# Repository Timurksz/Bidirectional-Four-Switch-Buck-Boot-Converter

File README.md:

This repository contains the design files and documentation for a 100W Bidirectional Four Switch Buck-Boost (FSBB) Converter, digitally controlled by the Texas Instruments UCD3138 microprocessor.

Featuring bidirectional energy transfer, this converter is ideal for battery management systems (BMS), automotive applications (48V/12V dual-battery systems), and renewable energy setups.

Project Overview

The topology is based on a non-isolated synchronous four-switch buck-boost converter, capable of operating in two primary modes:
- Buck Mode (48V → 12V): The high-voltage side supplies the low-voltage load.
- Boost Mode (12V → 48V): The low-voltage source transfers energy back to the 48V bus.

The system is digitally controlled using the UCD3138 microprocessor, enabling:
- Closed-loop voltage regulation
- PWM generation
- Bidirectional mode management
- Protection algorithms
- Real-time monitoring

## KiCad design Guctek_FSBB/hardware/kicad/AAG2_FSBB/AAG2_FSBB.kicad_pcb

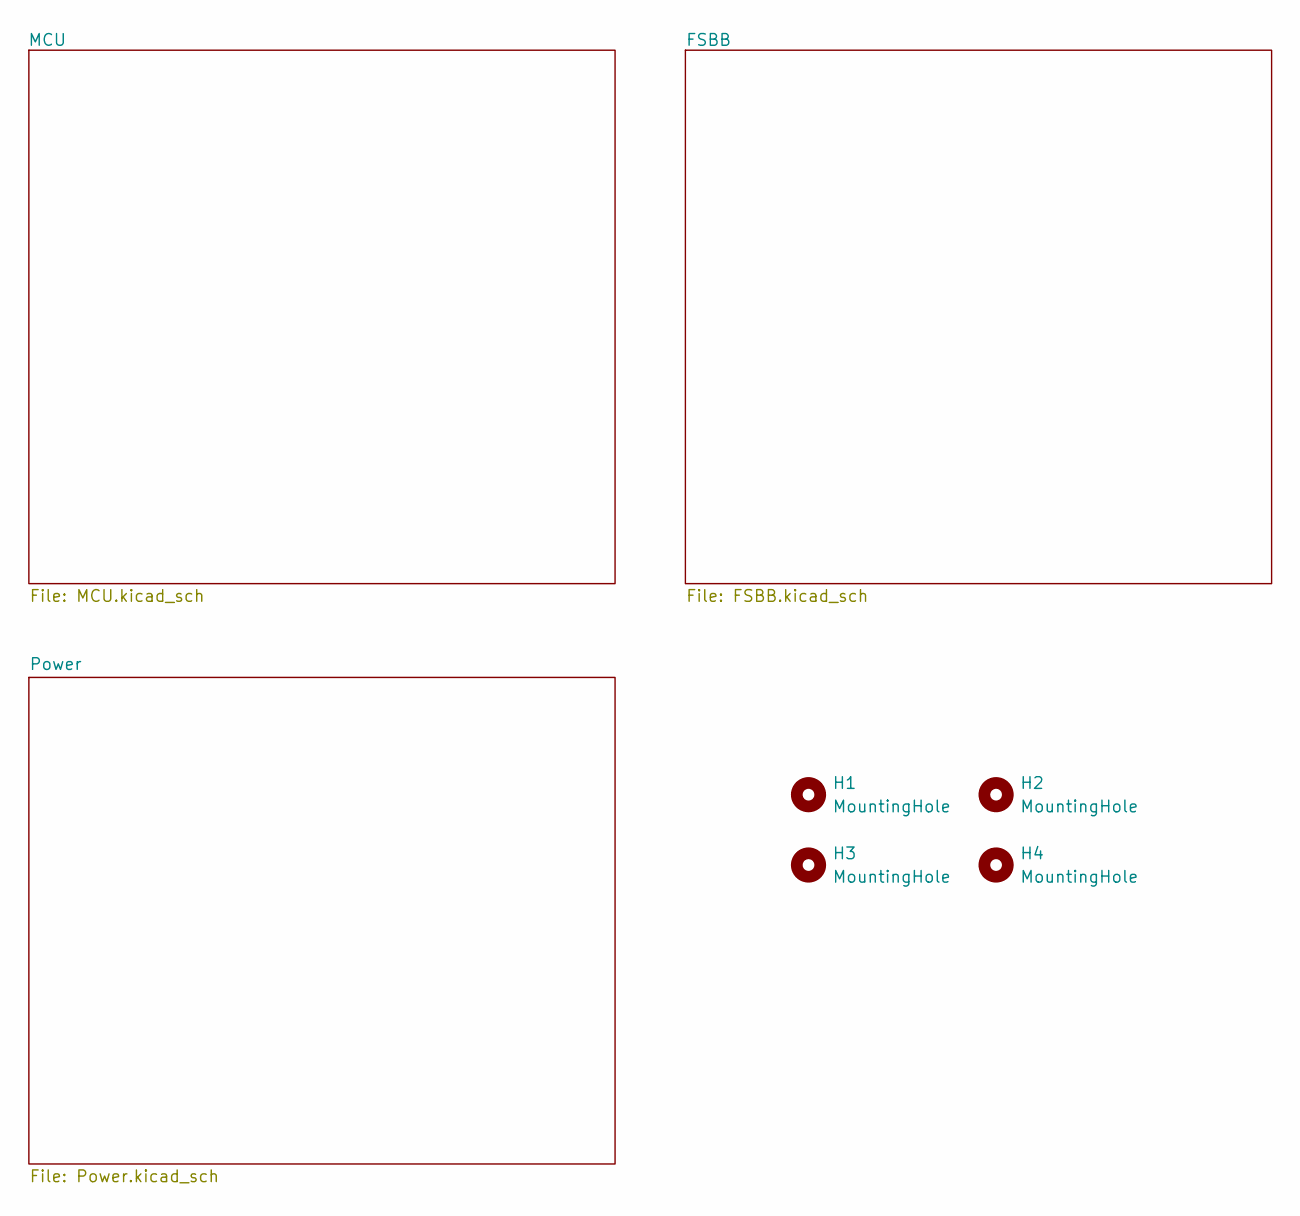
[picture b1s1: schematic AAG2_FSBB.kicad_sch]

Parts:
H1, H2, H3, H4: MountingHole; MountingHole_2.5mm_Pad

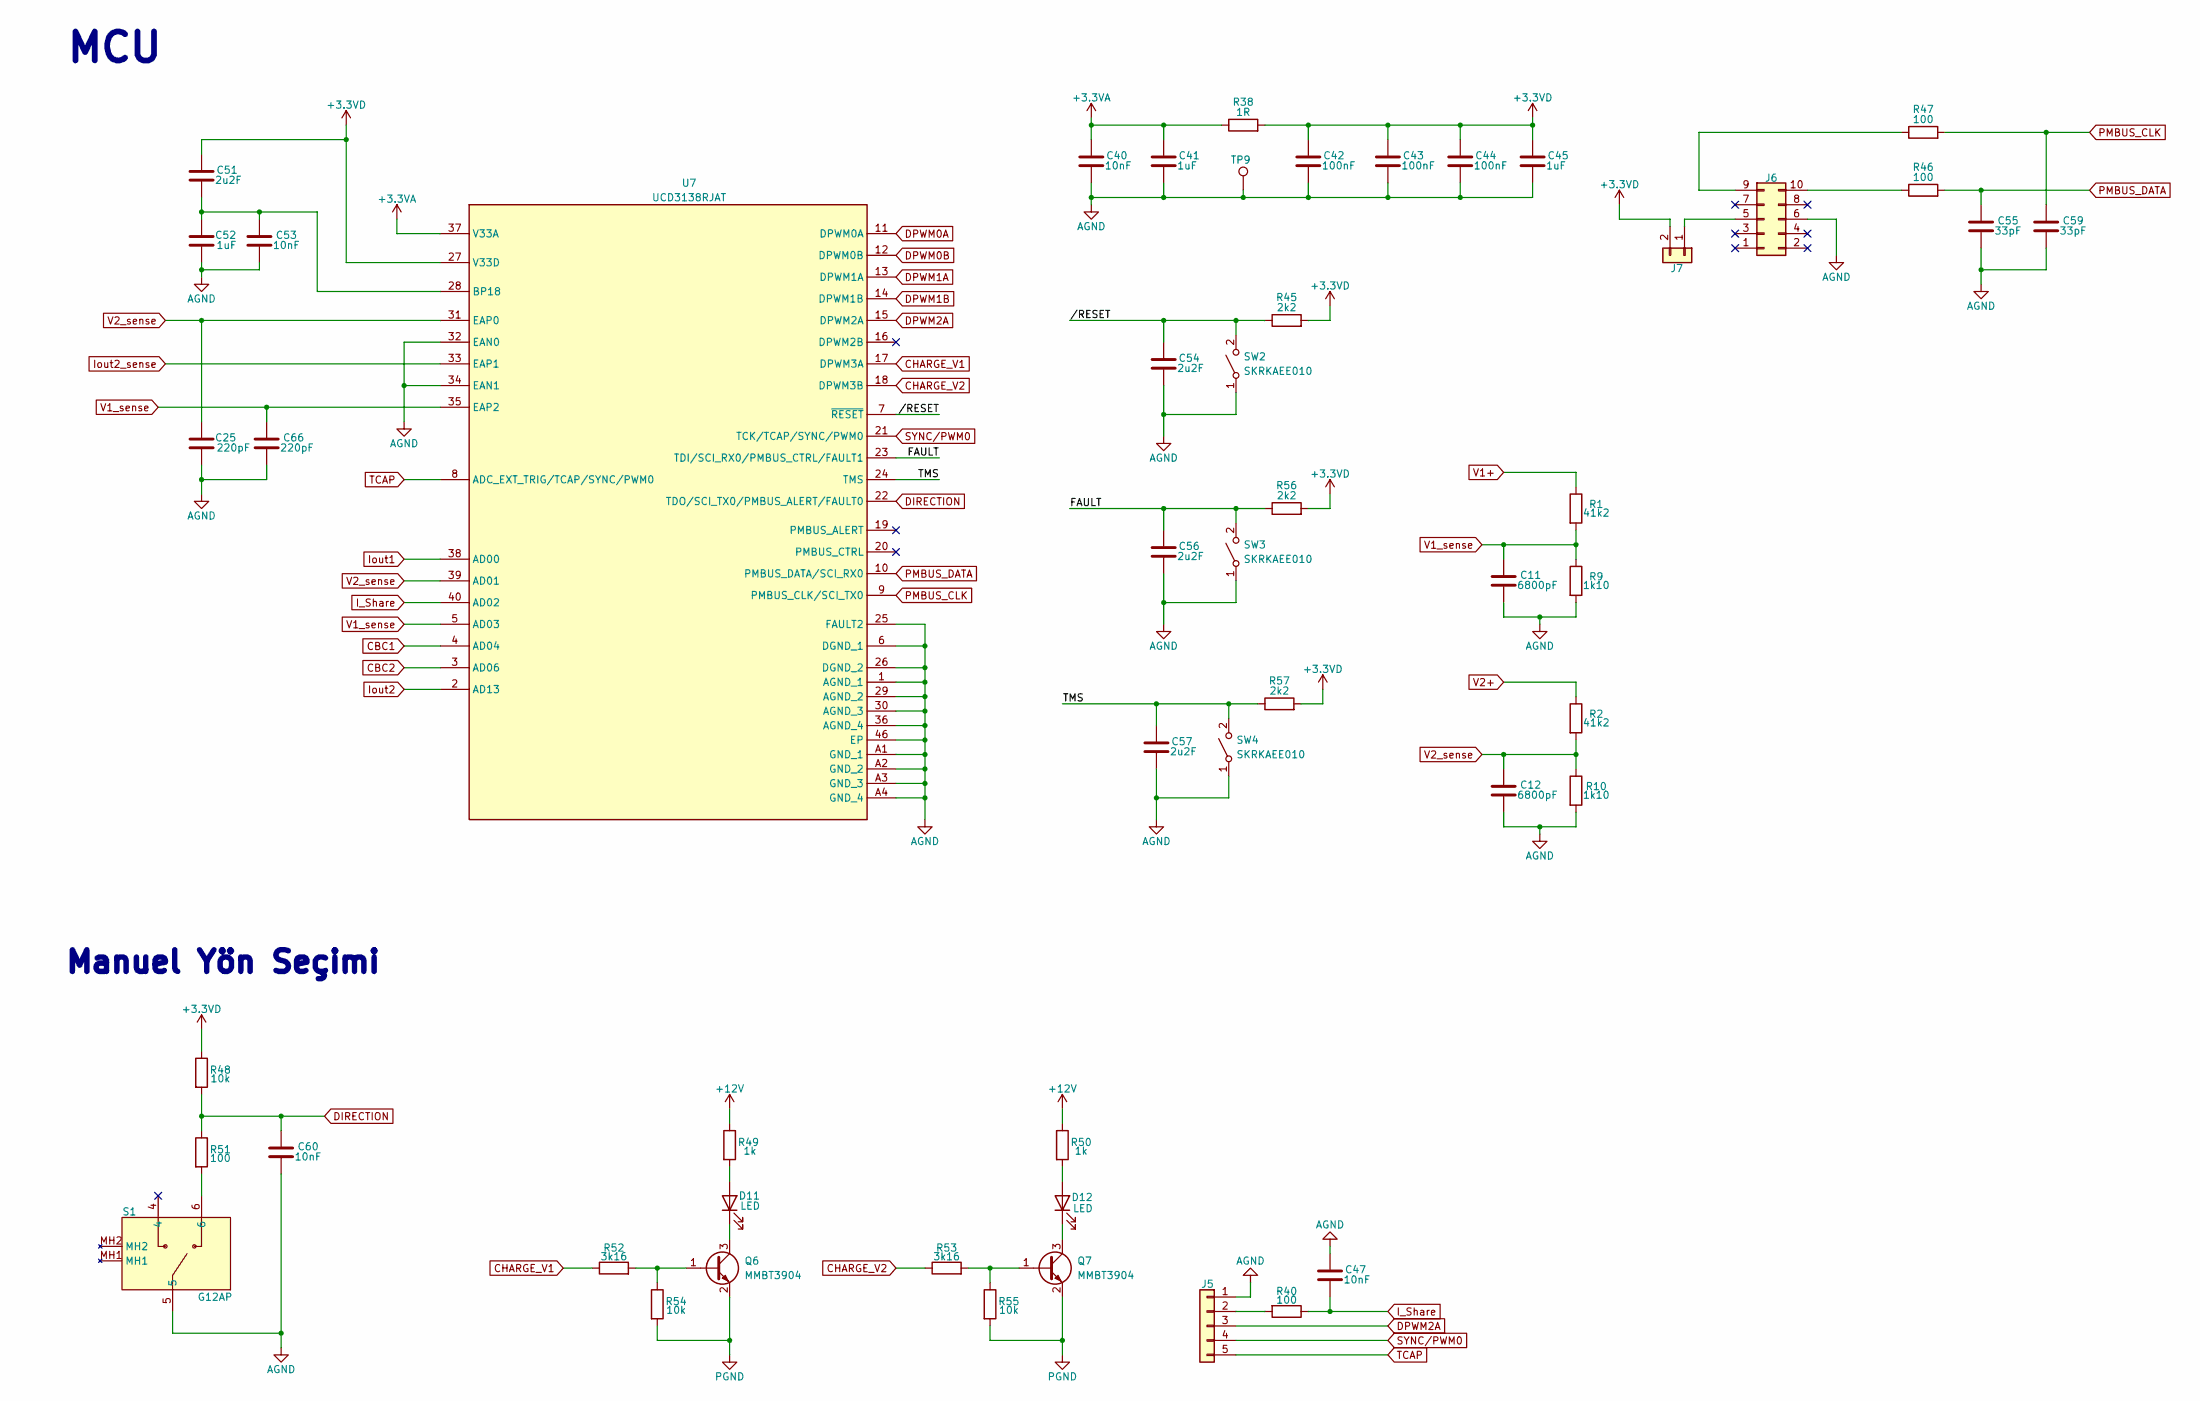
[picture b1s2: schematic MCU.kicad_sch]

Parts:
C11, C12: 6800pF; C_0603_1608Metric
C25, C66: 220pF; C_0603_1608Metric
C40, C47, C53, C60: 10nF; C_0603_1608Metric
C41, C45, C52: 1uF; C_0603_1608Metric
C42, C43, C44: 100nF; C_0603_1608Metric
C51, C54, C56, C57: 2u2F; C_0603_1608Metric
C55, C59: 33pF; C_0603_1608Metric
D11, D12: LED; LED_0805_2012Metric
J5: Conn_01x05; PinHeader_1x05_P1.00mm_Vertical
J6: 5103308-1
J7: Conn_01x02; PinHeader_01x02_P2.54mm_Vertical_THT_D1mm
Q6, Q7: MMBT3904; SOT-23
R1, R2: 41k2; R_0603_1608Metric
R9, R10: 1k10; R_0603_1608Metric
R38: 1R; R_0603_1608Metric
R40, R46, R47, R51: 100; R_0603_1608Metric
R45, R56, R57: 2k2; R_0603_1608Metric
R48, R54, R55: 10k; R_0603_1608Metric
R49, R50: 1k; R_0603_1608Metric
R52, R53: 3k16; R_0603_1608Metric
S1: G12AP; Manufacturer_Part_Number G12AP; Mouser Part Number 633-G12AP
SW2, SW3, SW4: SKRKAEE010
TP9: TestPoint; TestPoint_Pad_1.0x1.0mm
U7: UCD3138RJAT; Manufacturer_Part_Number UCD3138RJAT; Mouser Part Number 595-UCD3138RJAT

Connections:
+3.3VA: C40.1, C41.1, R38.1, U7.37 (V33A)
+3.3VD: C42.1, C43.1, C44.1, C45.1, C51.1, J7.2, R38.2, R45.2, R48.1, R56.2, R57.2, U7.27 (V33D); also elsewhere on the board
+12V: R49.1, R50.1; also elsewhere on the board
/MCU/FAULT: C56.1, R56.1, SW3.2 (B), U7.23 (TDI/SCI_RX0/PMBUS_CTRL/FAULT1)
/MCU/TMS: C57.1, R57.1, SW4.2 (B), U7.24 (TMS)
/MCU//RESET: C54.1, R45.1, SW2.2 (B), U7.7 (~RESET)
AGND: C11.2, C12.2, C25.2, C40.2, C41.2, C42.2, C43.2, C44.2, C45.2, C47.1, C52.2, C53.2, C54.2, C55.2, C56.2, C57.2, C59.2, C60.2, C66.2, J5.1, J6.6, R9.2, R10.2, S1.5, SW2.1 (A), SW3.1 (A), SW4.1 (A), TP9.1, U7.1 (AGND_1), U7.6 (DGND_1), U7.25 (FAULT2), U7.26 (DGND_2), U7.29 (AGND_2), U7.30 (AGND_3), U7.32 (EAN0), U7.34 (EAN1), U7.36 (AGND_4), U7.46 (EP), U7.A1 (GND_1), U7.A2 (GND_2), U7.A3 (GND_3), U7.A4 (GND_4); also elsewhere on the board
CBC1: U7.4 (AD04); also elsewhere on the board
CBC2: U7.3 (AD06); also elsewhere on the board
CHARGE_V1: R52.1, U7.17 (DPWM3A)
CHARGE_V2: R53.1, U7.18 (DPWM3B)
DIRECTION: C60.1, R48.2, R51.1, U7.22 (TDO/SCI_TX0/PMBUS_ALERT/FAULT0)
DPWM0A: U7.11 (DPWM0A); also elsewhere on the board
DPWM0B: U7.12 (DPWM0B); also elsewhere on the board
DPWM1A: U7.13 (DPWM1A); also elsewhere on the board
DPWM1B: U7.14 (DPWM1B); also elsewhere on the board
DPWM2A: J5.3, U7.15 (DPWM2A)
I_Share: C47.2, R40.1, U7.40 (AD02)
Iout1: U7.38 (AD00); also elsewhere on the board
Iout2: U7.2 (AD13); also elsewhere on the board
Iout2_sense: U7.33 (EAP1); also elsewhere on the board
unnamed: D11.2 (A), R49.2
unnamed: D11.1 (K), Q6.3 (C)
unnamed: D12.2 (A), R50.2
unnamed: D12.1 (K), Q7.3 (C)
unnamed: J5.2, R40.2
unnamed: J6.5, J7.1
unnamed: J6.9, R47.1
unnamed: J6.10, R46.1
unnamed: Q6.1 (B), R52.2, R54.1
unnamed: Q7.1 (B), R53.2, R55.1
unnamed: R51.2, S1.6
unnamed: C51.2, C52.1, C53.1, U7.28 (BP18)
PGND: Q6.2 (E), Q7.2 (E), R54.2, R55.2; also elsewhere on the board
PMBUS_CLK: C59.1, R47.2, U7.9 (PMBUS_CLK/SCI_TX0)
PMBUS_DATA: C55.1, R46.2, U7.10 (PMBUS_DATA/SCI_RX0)
SYNC/PWM0: J5.4, U7.21 (TCK/TCAP/SYNC/PWM0)
TCAP: J5.5, U7.8 (ADC_EXT_TRIG/TCAP/SYNC/PWM0)
V1+: R1.1; also elsewhere on the board
V1_sense: C11.1, C66.1, R1.2, R9.1, U7.5 (AD03), U7.35 (EAP2)
V2+: R2.1; also elsewhere on the board
V2_sense: C12.1, C25.1, R2.2, R10.1, U7.31 (EAP0), U7.39 (AD01)

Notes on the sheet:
MCU
Manuel Yön Seçimi

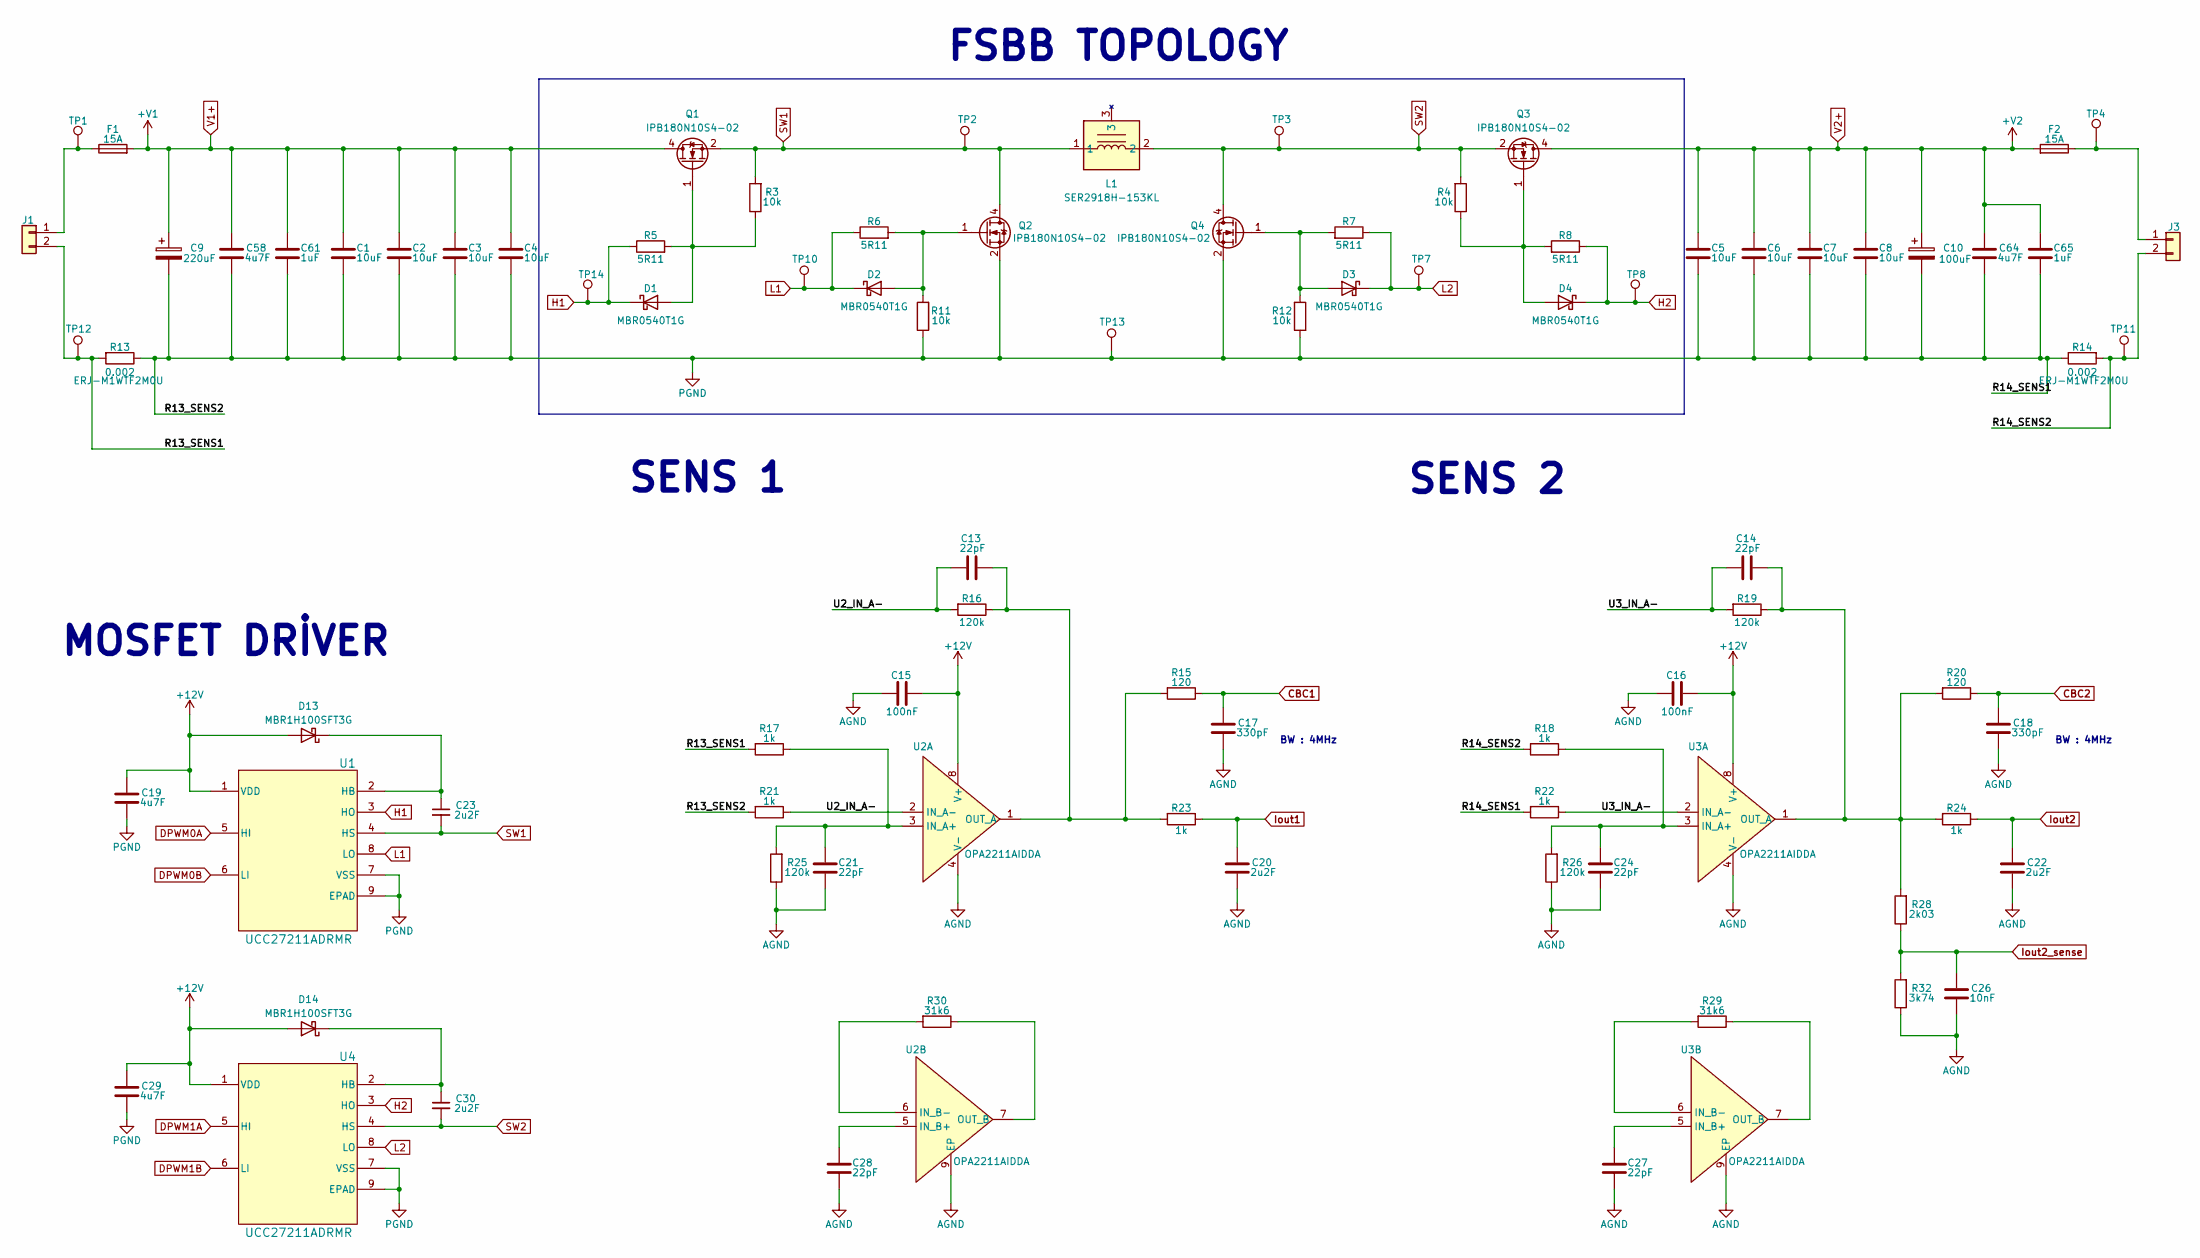
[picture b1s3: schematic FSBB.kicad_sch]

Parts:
C1, C2, C3, C4, C5, C6, C7, C8: 10uF; C_2220_5750Metric
C9: 220uF; EEEFK0J332AQ
C10: 100uF; CAPAE1300X1380N
C13, C14, C21, C24, C27, C28: 22pF; C_0603_1608Metric
C15, C16: 100nF; C_0603_1608Metric
C17, C18: 330pF; C_0603_1608Metric
C19, C29: 4u7F; C_0805_2012Metric
C20, C22: 2u2F; C_0603_1608Metric
C23, C30: 2u2F; C_1206_3216Metric
C26: 10nF; C_0603_1608Metric
C58, C64: 4u7F; C_1210_3225Metric
C61, C65: 1uF; C_1206_3216Metric
D1, D2, D3, D4: MBR0540T1G; D_SOD-123
D13, D14: MBR1H100SFT3G; SODFL3616X98N
F1, F2: 15A; SS_BEL
J1, J3: Conn_01x02; ED1202DS
L1: SER2918H-153KL; SER2918H333KL; Manufacturer_Part_Number SER2918H-153KL; Mouser Part Number 994-SER2918H-153KL
Q1, Q2, Q3, Q4: IPB180N10S4-02; TO-263-6
R3, R4, R11, R12: 10k; R_0603_1608Metric
R5, R6, R7, R8: 5R11; R_0805_2012Metric
R13, R14: 0.002; R_2512_6332Metric
R15, R20: 120; R_0603_1608Metric
R16, R19, R25, R26: 120k; R_0603_1608Metric
R17, R18, R21, R22, R23, R24: 1k; R_0603_1608Metric
R28: 2k03; R_0603_1608Metric
R29, R30: 31k6; R_0603_1608Metric
R32: 3k74; R_0603_1608Metric
TP1, TP2, TP3, TP4, TP7, TP8, TP10, TP11, TP12, TP13, TP14: TestPoint; TestPoint_Pad_1.0x1.0mm
U1, U4: UCC27211ADRMR; DRM8_3P38X2P45_TEX
U2, U3: OPA2211AIDDA; SOIC127P600X170-9N

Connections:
+12V: C15.2, C16.2, C19.1, C29.1, D13.2 (A), D14.2 (A), U1.1 (VDD), U2.8 (V+), U3.8 (V+), U4.1 (VDD); also elsewhere on the board
/FSBB/R13_SENS1: J1.2, R13.2, R17.2, TP12.1; also elsewhere on the board
/FSBB/R14_SENS2: J3.2, R14.2, R18.2, TP11.1; also elsewhere on the board
/FSBB/U2_IN_A-: C13.1, R16.2, R21.1, U2.2 (IN_A-)
/FSBB/U3_IN_A-: C14.1, R19.2, R22.1, U3.2 (IN_A-)
AGND: C15.1, C16.1, C17.2, C18.2, C20.2, C21.2, C22.2, C24.2, C26.2, C27.2, C28.2, R25.1, R26.1, R32.1, U2.4 (V-), U2.9 (EP), U3.4 (V-), U3.9 (EP); also elsewhere on the board
CBC1: C17.1, R15.1; also elsewhere on the board
CBC2: C18.1, R20.1; also elsewhere on the board
DPWM0A: U1.5 (HI); also elsewhere on the board
DPWM0B: U1.6 (LI); also elsewhere on the board
DPWM1A: U4.5 (HI); also elsewhere on the board
DPWM1B: U4.6 (LI); also elsewhere on the board
H1: D1.1 (K), R5.1, TP14.1, U1.3 (HO); also elsewhere on the board
H2: D4.1 (K), R8.1, TP8.1, U4.3 (HO); also elsewhere on the board
Iout1: C20.1, R23.1; also elsewhere on the board
Iout2: C22.1, R24.1; also elsewhere on the board
Iout2_sense: C26.1, R28.1, R32.2; also elsewhere on the board
L1: D2.1 (K), R6.1, TP10.1, U1.8 (LO); also elsewhere on the board
unnamed: D1.2 (A), Q1.1 (G), R3.1, R5.2
unnamed: D2.2 (A), Q2.1 (G), R6.2, R11.2
unnamed: D3.2 (A), Q4.1 (G), R7.2, R12.2
unnamed: D4.2 (A), Q3.1 (G), R4.1, R8.2
unnamed: C23.1, D13.1 (K), U1.2 (HB)
unnamed: C30.1, D14.1 (K), U4.2 (HB)
unnamed 41: F1.1, J1.1, TP1.1; also elsewhere on the board
unnamed 42: F2.1, J3.1, TP4.1; also elsewhere on the board
unnamed: C21.1, R17.1, R25.2, U2.3 (IN_A+)
unnamed: C13.2, R15.2, R16.1, R23.2, U2.1 (OUT_A)
unnamed: C28.1, U2.5 (IN_B+)
unnamed: R30.2, U2.6 (IN_B-)
unnamed: R30.1, U2.7 (OUT_B)
unnamed: C24.1, R18.1, R26.2, U3.3 (IN_A+)
unnamed: C14.2, R19.1, R20.2, R24.2, R28.2, U3.1 (OUT_A)
unnamed: C27.1, U3.5 (IN_B+)
unnamed: R29.2, U3.6 (IN_B-)
unnamed: R29.1, U3.7 (OUT_B)
PGND: C1.2, C2.2, C3.2, C4.2, C5.2, C6.2, C7.2, C8.2, C9.2, C10.2, C19.2, C29.2, C58.2, C61.2, C64.2, C65.2, Q2.2 (S), Q2.3 (S), Q2.5 (S), Q2.6 (S), Q2.7 (S), Q4.2 (S), Q4.3 (S), Q4.5 (S), Q4.6 (S), Q4.7 (S), R11.1, R12.1, R13.1, R14.1, R21.2, R22.2, TP13.1, U1.7 (VSS), U1.9 (EPAD), U4.7 (VSS), U4.9 (EPAD); also elsewhere on the board
SW1: C23.2, L1.1, Q1.2 (S), Q1.3 (S), Q1.5 (S), Q1.6 (S), Q1.7 (S), Q2.4 (D), R3.2, TP2.1, U1.4 (HS); also elsewhere on the board
SW2: C30.2, L1.2, Q3.2 (S), Q3.3 (S), Q3.5 (S), Q3.6 (S), Q3.7 (S), Q4.4 (D), R4.2, TP3.1, U4.4 (HS); also elsewhere on the board
V1+: C1.1, C2.1, C3.1, C4.1, C9.1, C58.1, C61.1, F1.2, Q1.4 (D); also elsewhere on the board
V2+: C5.1, C6.1, C7.1, C8.1, C10.1, C64.1, C65.1, F2.2, Q3.4 (D); also elsewhere on the board

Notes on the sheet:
SENS 2
BW : 4MHz
SENS 1
MOSFET DRİVER
FSBB TOPOLOGY

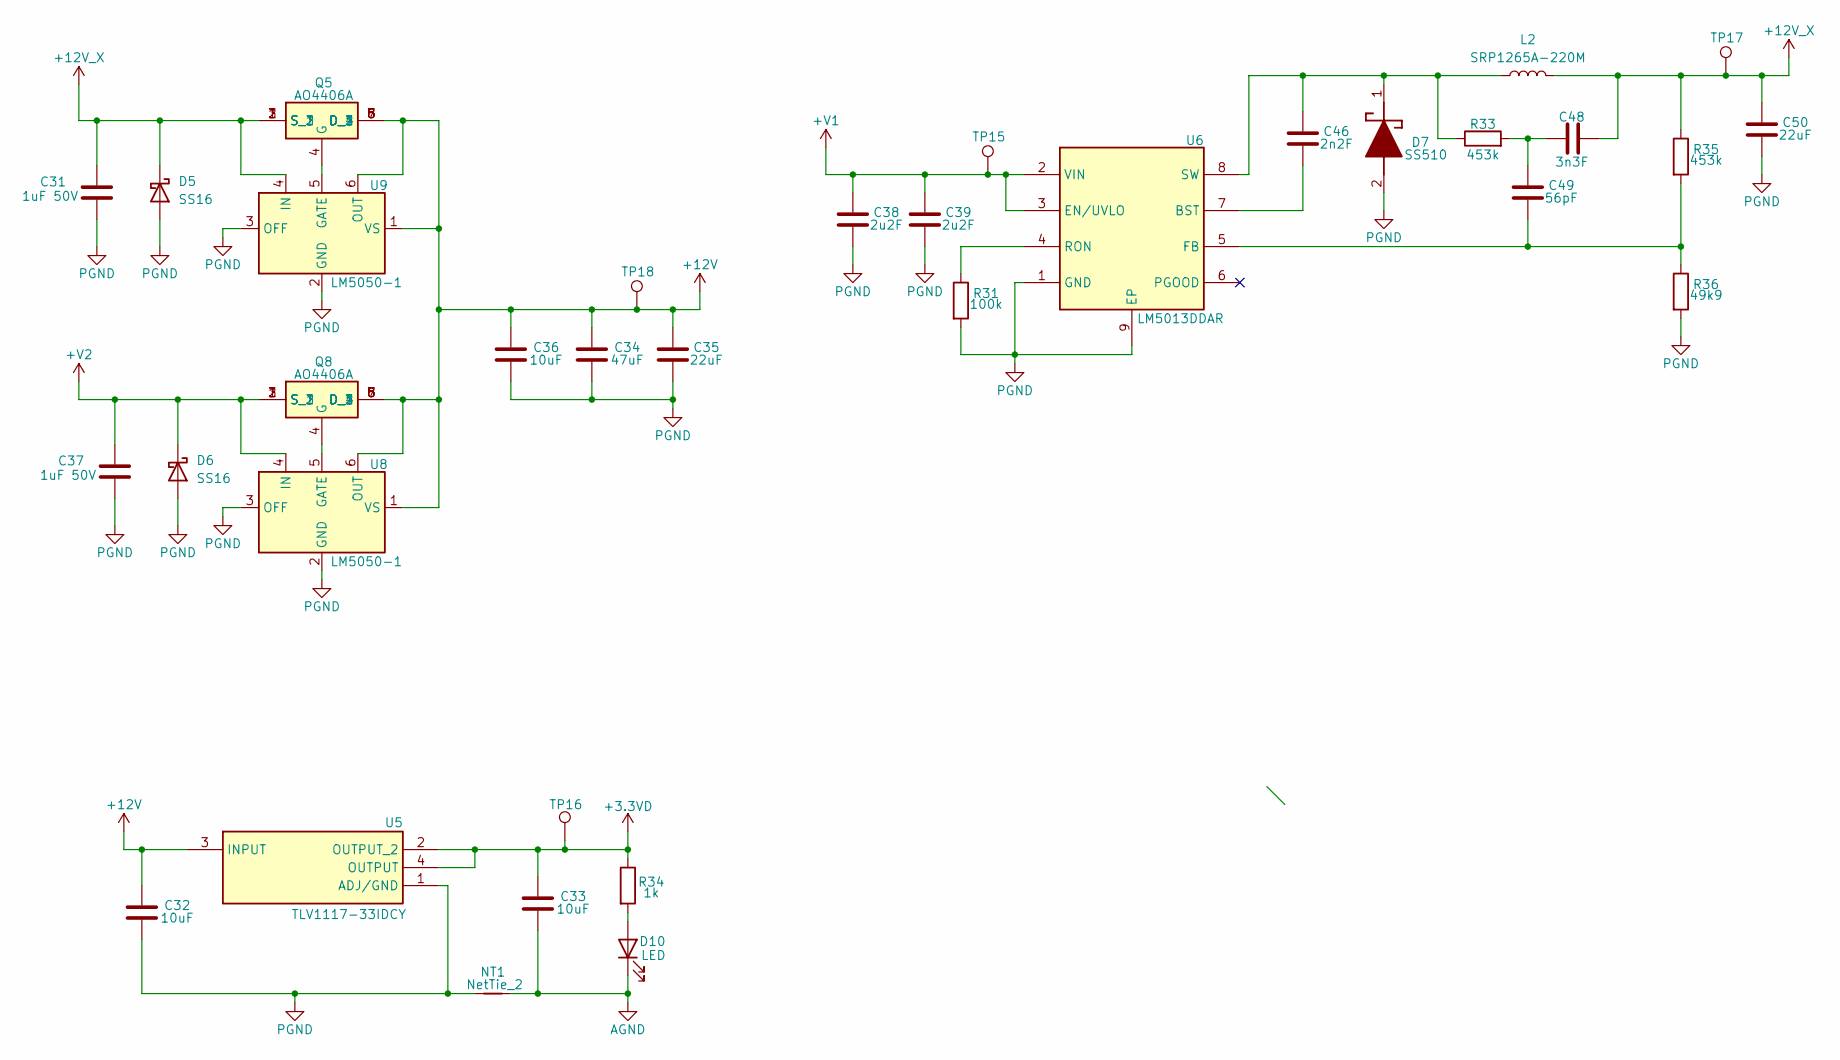
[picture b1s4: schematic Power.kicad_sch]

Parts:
C31, C37: 1uF 50V; C_0603_1608Metric
C32, C36: 10uF; C_0805_2012Metric
C33: 10uF; C_0603_1608Metric
C34: 47uF; C_0805_2012Metric
C35: 22uF; C_0805_2012Metric
C38, C39: 2u2F; C_1210_3225Metric
C46: 2n2F; C_0603_1608Metric
C48: 3n3F; C_0603_1608Metric
C49: 56pF; C_0603_1608Metric
C50: 22uF; C_1210_3225Metric
D5, D6: SS16; D_SMA
D7: SS510; DIONM7959X262N; Manufacturer_Part_Number SS510
D10: LED; LED_0805_2012Metric
L2: SRP1265A-220M; SRP1265A
NT1: NetTie_2; NetTie-2_SMD_Pad0.5mm
Q5, Q8: AO4406A; SOIC127P600X175-8N; Manufacturer_Part_Number AO4406A; LCSC PART C2944312
R31: 100k; R_0603_1608Metric
R33, R35: 453k; R_0603_1608Metric
R34: 1k; R_0603_1608Metric
R36: 49k9; R_0603_1608Metric
TP15, TP16, TP17, TP18: TestPoint; TestPoint_Pad_1.0x1.0mm
U5: TLV1117-33IDCY; SOT230P700X180-4N; Manufacturer_Part_Number TLV1117-33IDCY; Mouser Part Number 595-TLV1117-33IDCY
U6: LM5013DDAR; SOIC127P600X170-9N; Manufacturer_Part_Number LM5013DDAR; Mouser Part Number 595-LM5013DDAR
U8, U9: LM5050-1; TSOT-23-6; LCSC PART C129323

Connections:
+3.3VD: C33.1, R34.1, TP16.1, U5.2 (OUTPUT_2), U5.4 (OUTPUT); also elsewhere on the board
+12V: C32.1, C34.1, C35.1, C36.1, Q5.5 (D_1), Q5.6 (D_2), Q5.7 (D_3), Q5.8 (D_4), Q8.5 (D_1), Q8.6 (D_2), Q8.7 (D_3), Q8.8 (D_4), TP18.1, U5.3 (INPUT), U8.1 (VS), U8.6 (OUT), U9.1 (VS), U9.6 (OUT); also elsewhere on the board
AGND: C33.2, D10.1 (K), NT1.2; also elsewhere on the board
unnamed: C48.1, C49.1, R33.2
unnamed 33: C46.1, D7.1 (K), L2.2, R33.1, U6.8 (SW); also elsewhere on the board
unnamed: D10.2 (A), R34.2
unnamed: Q5.4 (G), U9.5 (GATE)
unnamed: Q8.4 (G), U8.5 (GATE)
unnamed: C46.2, U6.7 (BST)
unnamed: C49.2, R35.2, R36.1, U6.5 (FB)
unnamed: R31.1, U6.4 (RON)
PGND: C31.2, C32.2, C34.2, C35.2, C36.2, C37.2, C38.2, C39.2, C50.2, D5.2 (A), D6.2 (A), D7.2 (A), NT1.1, R31.2, R36.2, U5.1 (ADJ/GND), U6.1 (GND), U6.9 (EP), U8.2 (GND), U8.3 (OFF), U9.2 (GND), U9.3 (OFF); also elsewhere on the board
V1+: C38.1, C39.1, TP15.1, U6.2 (VIN), U6.3 (EN/UVLO); also elsewhere on the board
V2+: C37.1, D6.1 (K), Q8.1 (S_1), Q8.2 (S_2), Q8.3 (S_3), U8.4 (IN); also elsewhere on the board

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
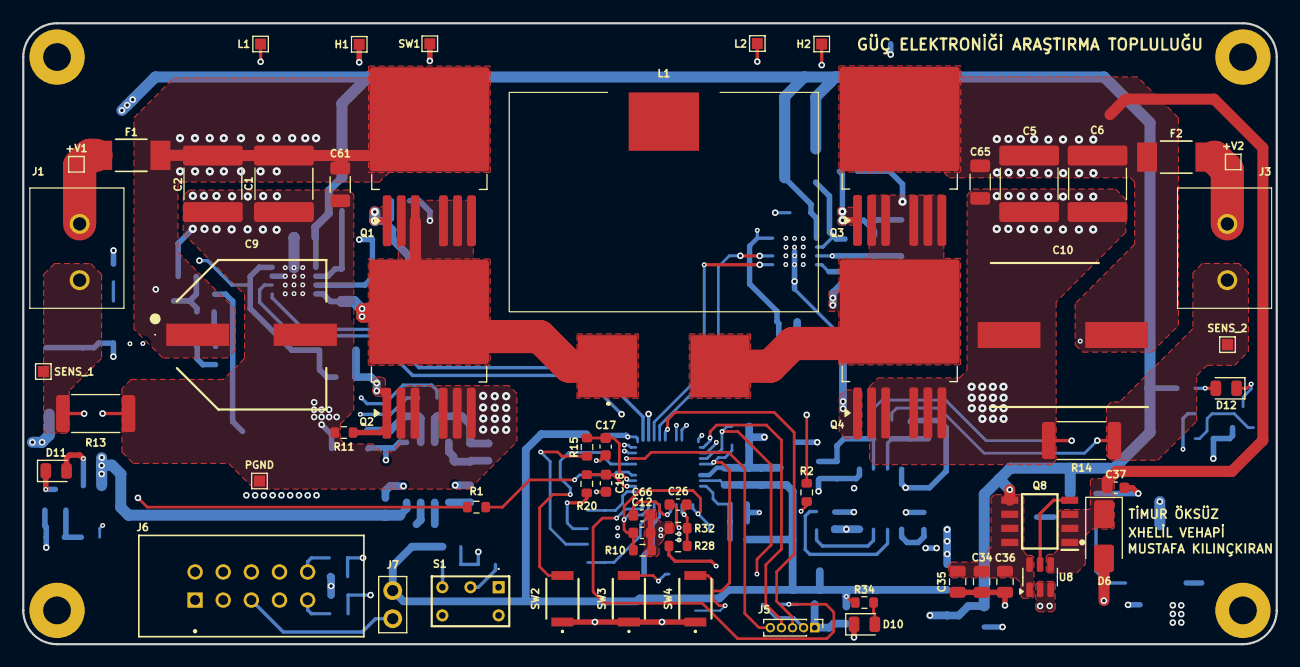
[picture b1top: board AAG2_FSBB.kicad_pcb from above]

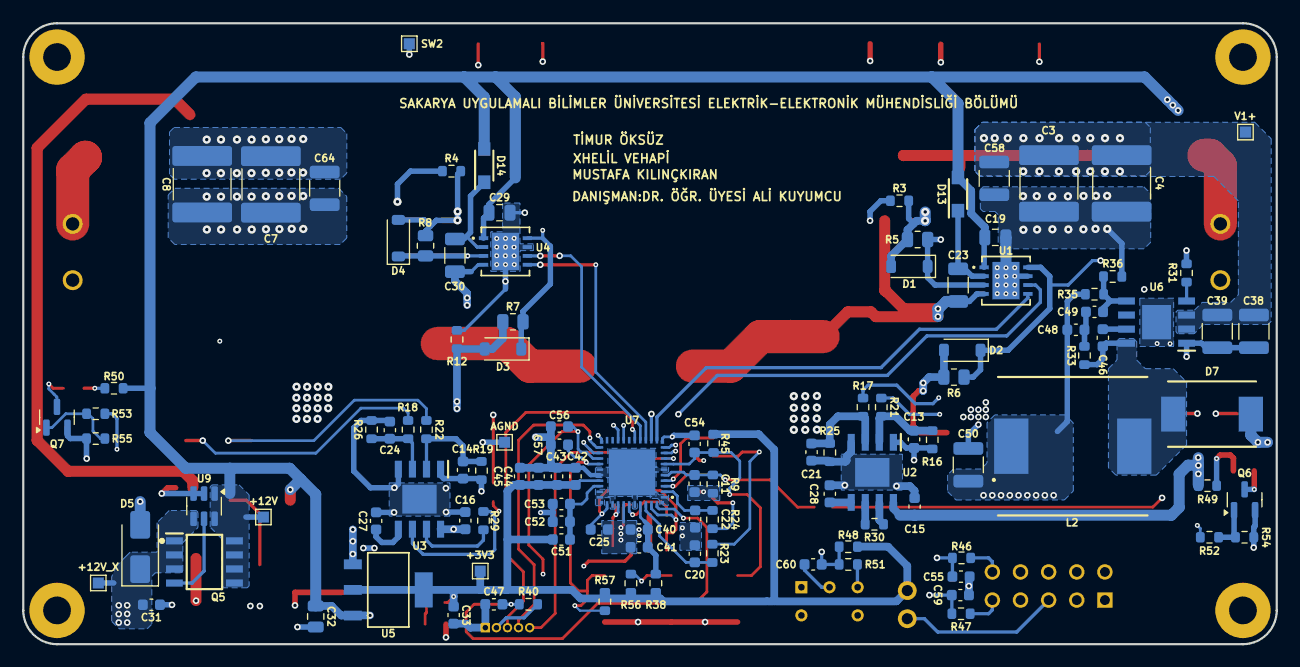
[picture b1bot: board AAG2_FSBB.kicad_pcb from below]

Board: 4 copper layers, 113.2 x 56.1 mm, 177 parts (113 on the bottom side), 79 nets.

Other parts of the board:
+3V3, +12V, +12V_X: TestPoint; TestPoint_Pad_1.0x1.0mm
+V1, +V2: TestPoint; TestPoint_Pad_1.0x1.0mm
AGND: TestPoint; TestPoint_Pad_1.0x1.0mm
H1#2, H2#2: TestPoint; TestPoint_Pad_1.0x1.0mm
L1#2: TestPoint; TestPoint_Pad_1.0x1.0mm
L2#2: SRP1265A-220M; SRP1265A
PGND: TestPoint; TestPoint_Pad_1.0x1.0mm
SENS_1, SENS_2: TestPoint; TestPoint_Pad_1.0x1.0mm
SW1, SW2#2: TestPoint; TestPoint_Pad_1.0x1.0mm
V1+: TestPoint; TestPoint_Pad_1.0x1.0mm

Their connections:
+3.3VD: +3V3.1; also elsewhere on the board
+12V: +12V.1; also elsewhere on the board
/FSBB/R13_SENS1: SENS_1.1; also elsewhere on the board
/FSBB/R14_SENS2: SENS_2.1; also elsewhere on the board
AGND: AGND.1; also elsewhere on the board
H1: H1#2.1; also elsewhere on the board
H2: H2#2.1; also elsewhere on the board
L1: L1#2.1; also elsewhere on the board
unnamed 33: L2#2.2; also elsewhere on the board
unnamed 41: +V1.1; also elsewhere on the board
unnamed 42: +V2.1; also elsewhere on the board
PGND: PGND.1; also elsewhere on the board
SW1: SW1.1; also elsewhere on the board
SW2: SW2#2.1; also elsewhere on the board
V1+: V1+.1; also elsewhere on the board

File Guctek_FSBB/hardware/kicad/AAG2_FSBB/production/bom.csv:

Designator,Footprint,Quantity,Value,LCSC Part #
"+12V, +12V_X, +3V3, +V1, +V2, AGND, H1_2, H2_2, L1, L2_2, PGND, SENS_1, SENS_2, SW1, SW2, V1+",TestPoint_Pad_1.0x1.0mm,16,TestPoint,
"C1, C2, C3, C4, C5, C6, C7, C8",2220,8,10uF,
C10,CAPAE1300X1380N,1,100uF,
"C11, C12",0603,2,6800pF,
"C13, C14, C21, C24, C27, C28",0603,6,22pF,
"C15, C16, C42, C43, C44",0603,5,100nF,
"C17, C18",0603,2,330pF,
"C19, C29",0805,2,4u7F,
"C20, C22, C51, C54, C56, C57",0603,6,2u2F,
"C23, C30",1206,2,2u2F,
"C25, C66",0603,2,220pF,
"C26, C40, C47, C53, C60",0603,5,10nF,
"C31, C37",0603,2,1uF 50V,
"C32, C36",0805,2,10uF,
C33,0603,1,10uF,
C34,0805,1,47uF,
C35,0805,1,22uF,
"C38, C39",1210,2,2u2F,
"C41, C45, C52",0603,3,1uF,
C46,0603,1,2n2F,
C48,0603,1,3n3F,
C49,0603,1,56pF,
C50,1210,1,22uF,
"C55, C59",0603,2,33pF,
"C58, C64",1210,2,4u7F,
"C61, C65",1206,2,1uF,
C9,EEEFK0J332AQ,1,220uF,
"D1, D2, D3, D4",D_SOD-123,4,MBR0540T1G,
"D10, D11, D12",0805,3,LED,
"D13, D14",SODFL3616X98N,2,MBR1H100SFT3G,
"D5, D6",D_SMA,2,SS16,
D7,DIONM7959X262N,1,SS510,
"F1, F2",SS_BEL,2,15A,
"J1, J3",ED1202DS,2,Conn_01x02,
J5,PinHeader_1x05_P1.00mm_Vertical,1,Conn_01x05,
J6,5103308-1,1,5103308-1,
J7,PinHeader_01x02_P2.54mm_Vertical_THT_D1mm,1,Conn_01x02,
L1_2,SER2918H333KL,1,SER2918H-153KL,
L2,SRP1265A,1,SRP1265A-220M,
"Q1, Q2, Q3, Q4",TO-263-6,4,IPB180N10S4-02,
"Q5, Q8",SOIC127P600X175-8N,2,AO4406A,
"Q6, Q7",SOT-23,2,MMBT3904,
"R1, R2",0603,2,41k2,
"R10, R9",0603,2,1k10,
"R11, R12, R3, R4, R48, R54, R55",0603,7,10k,
"R13, R14",2512,2,0.002,
"R15, R20",0603,2,120,
"R16, R19, R25, R26",0603,4,120k,
"R17, R18, R21, R22, R23, R24, R34, R49, R50",0603,9,1k,
R28,0603,1,2k03,
"R29, R30",0603,2,31k6,
R31,0603,1,100k,
R32,0603,1,3k74,
"R33, R35",0603,2,453k,
R36,0603,1,49k9,
R38,0603,1,1R,
"R40, R46, R47, R51",0603,4,100,
"R45, R56, R57",0603,3,2k2,
"R5, R6, R7, R8",0805,4,5R11,
"R52, R53",0603,2,3k16,
S1,G12AP,1,G12AP,
"SW2_2, SW3, SW4",SKRKAEE010,3,SKRKAEE010,
"U1, U4",DRM8_3P38X2P45_TEX,2,UCC27211ADRMR,
"U2, U3",SOIC127P600X170-9N,2,OPA2211AIDDA,
U5,SOT230P700X180-4N,1,TLV1117-33IDCY,
U6,SOIC127P600X170-9N,1,LM5013DDAR,
U7,UCD3138RJAT,1,UCD3138RJAT,
"U8, U9",TSOT-23-6,2,LM5050-1,

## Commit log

2026-05-19 Bidirectional Four Switch Buck Boot Converter
    Bidirectional Four Switch Buck Boot Converter (48V-12V)
2026-05-19 Add README with project details for FSBB Converter
    Added project overview and details about the FSBB Converter.
